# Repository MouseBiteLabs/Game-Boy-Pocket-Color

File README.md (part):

# Game Boy Pocket Color

My <a href="https://github.com/MouseBiteLabs/Game-Boy-DMG-Color">DMGC project</a> put a Game Boy Color put into an original Game Boy shell. But then I said, "Hey! This is neat, but I would rather it be small and cramped and have shorter battery life!" Enter the MGBC, or Pocket Color - a Game Boy Pocket (model name MGB) with the guts of a Game Boy Color (GBC). The PCB here is an original creation with some new features, though the concept and implementation of the "MGBC" or "Pocket Color" has been around for a while! Here are the project goals:

- A Game Boy Pocket aesthetic, using the original Game Boy Pocket shell and interfaces (link port, volume wheel, power switch, etc.), but with the capability of playing both Game Boy and Game Boy Color games.
- A nice, large IPS screen – the GBC Q5 XL IPS Backlight with OSD kit – with brightness and color palette control via the "navigation switch" housed where the contrast wheel used to be. (I will refer to the PCB attached to the Q5 screen as the “Q5 board”)
- A modernized, efficient switch mode power supply that can run off 2x AAA batteries or input from the DC jack, just like the original MGB. Testing shows that playing with NiMH AAA batteries can yield about 3.5 hours of gameplay at normal settings.
- Louder, cleaner sound through a modern audio amplifier.
- The option for tactile switches for the face buttons - like the GBA SP.
- No major externally viewable case modifications, to keep the OEM look and feel, outside of the screen, as much as possible.

All gerbers and source files can be found in this repo, as this project is fully open source. These PCB files and notes about the board, including customizations **and some troubleshooting tips**, can be found in the <a href="https://github.com/MouseBiteLabs/Game-Boy-Pocket-Color/tree/main/MGBC%20PCB#cpu-pin-functions">PCB folder</a>. Technical documentation of the board can be found in the <a href="https://github.com/MouseBiteLabs/Game-Boy-Pocket-Color/tree/main/Technical">Technical folder</a>.

**Do you want to make one?** Then you NEED TO READ this entire page. Seriously. Before asking a question, please review the <a href="https://github.com/MouseBiteLabs/Game-Boy-Pocket-Color#frequently-asked-questions">FAQ</a> at the bottom of the README for answers to.... frequently asked questions. Please try to find your answer in this repository - 95% of the time someone asks me something it's answered here already.

## Disclaimer

Before I go any further, please read this VERY important disclaimer, **IN IT'S ENTIRETY,** if you are thinking about making this yourself. **Don't let this picture happen to you!**

I made this project first and foremost for my own purposes. Nearly all of the features I have included are things I personally wanted. I have tried my hardest to make the project modular, if others would like to improve or change things easily, and I have also tried very hard to make the design somewhat less prone to potential errors during assembly. But in the end, every decision I made was for what I wanted the final product to be, with my skill level in mind.

So if you choose to build this project yourself, be warned - this is a considerably advanced, and expensive build. You must be comfortable with the fact that you may lose or damage expensive components. You are 100% liable for any damage done to your property or yourself. I am not responsible for any damage or loss of property incurred while attempting this project, or after completion of the project - you alone accept all risk. If you're *at all* questioning wether or not you can successfully attempt this project, please first practice with the <a href="https://github.com/MouseBiteLabs/Pocket-Mouse-Power-Board">Pocket Mouse Power Board</a> - this requires no original Game Boy parts, and the total parts cost of the board is less than $10. And before you dismantle a Game Boy, solder the FFC connector on the top of the MGBC board to make sure you are comfortable with long rows of fine pitch pins, as it is the same pin pitch as the much more expensive and important CPU. **If you have any difficulty assembling either the power board or the FFC connector, I highly discourage attempting the rest of the build.**

Furthermore, while I am confident in this design, I cannot claim full compatibility with every system configuration. **Especially if you decide to add a lithium-ion battery.** And there may be latent issues that have yet to crop up. If you see anything I may have missed, or some dubious design choice, feel free to ask questions or comment as such - feedback is appreciated, corrections are welcome.

In summation: **DO NOT attempt this project if you are uncomfortable or inexperienced with detailed electronics troubleshooting, or are not proficient in soldering! This is in NO WAY a beginner's project. You will AT MINIMUM need to be proficient in <a href="https://youtu.be/5uiroWBkdFY?t=110">drag soldering</a> and <a href="https://youtu.be/X3Rc1s6EpSI">hot air reflowing</a>. If you have not gained proficiency in these soldering skills, DO NOT ATTEMPT THIS PROJECT. You accept all risks and costs associated to this build if you choose to attempt it.**

(These parts are *tiny*. Quarter for scale - do not install a quarter in your final build.)

## Bill of Materials (BOM)

There are a handful of categories for the parts you need for this build. Please review all of them! The total BOM cost will come out to anywhere between $100 and $200 (NOT including the cost of a donor Game Boy Color console!) depending on the options you choose, which OEM parts you re-use, and any potential deals you can get on certain parts. Note that with the exception of a few components from a donor Game Boy Color, *most* of the electronic parts are brand new.

### I. Circuit Boards
  
First and foremost, you will need two brand new circuit boards for this build:
- <a href="https://github.com/MouseBiteLabs/Game-Boy-Pocket-Color/tree/main/MGBC%20PCB#mgbc-mbl-01">the main MGBC circuit board</a>, and 
- a power supply board that fits in the U5 socket on the MGBC board (like my <a href="https://github.com/MouseBiteLabs/Pocket-Mouse-Power-Board">Pocket Mouse Power Board</a>, or other power supply boards from other creators - check the <a href="https://github.com/MouseBiteLabs/Game-Boy-Pocket-Color#v-compatibility-with-other-mods">Compatibility</a> section below for more information. )

**I don't recommend using an original power board from a Game Boy!**

Again, I sell <a href="https://mousebitelabs.etsy.com/listing/1459241814/game-boy-pocket-color-pcb-mgbc-mbl-01?utm_source=Copy&utm_medium=ListingManager&utm_campaign=Share&utm_term=so.lmsm&share_time=1694127166906">the MGBC board</a> and <a href="https://mousebitelabs.etsy.com/listing/1473483915/pocket-mouse-power-board?utm_source=Copy&utm_medium=ListingManager&utm_campaign=Share&utm_term=so.lmsm&share_time=1694127201480">my regulator board</a> on my Etsy store. You can alternatively use the files in the MGBC PCB folder to order it yourself. Please see the MGBC PCB folder for more info.

And finally, <a href="https://shop.insidegadgets.com/product/game-boy-pocket-color/">insideGadgets sells these boards partially assembled!</a>

### Information on Older Revisions

The current revision is v2.1, but you may have an earlier board (if you bought one from me, rest assured it will work perfectly fine - most of the changes between for-sale revisions are inconsequential to the end user). The BOM has changed slightly for v1.6 and later boards, compared to previous revisions. Please view the Excel and/or .csv file above for BOM information (or contact me). Here's a short list of information about the older boards, and what is required/recommended when using them:

| Revision | Recommendations |
| ---- | ---------------------------------------------------------------------------------------------------------------------------- |
| v1.0 | You are a masochist. You're on your own for this one.                                                                        |
| v1.1 | Are you me? No? Then did you rob my house?                                                                                   |
| v1.2 | You're one of the beloved beta testers. You didn't build it yet? For shame. Contact me.                                      |
| v1.3 | These should be practice boards only.                                                                                        |
| v1.4 | Use tactile buttons. Minor shell trimming may be required for volume dial and rocker switch.                                 |
| v1.5 | Minor shell trimming may be required for volume dial and rocker switch.                                                      |
| v1.6 | No important differences compared to the latest revision, but check EM7 and DC/BT+ requirements!                             |
| v2.0 | No important differences compared to the latest revision.                                                                    |

### II. Brand New Electronic Parts

The MGBC board uses mostly all-new components. This is not a direct-transfer board. The master BOM with every electronic component required for the main MGBC circuit board is provided in the folder in Excel format. Note that some parts may be out of stock at the links provided, but many can be found at alternate other retailers online, or have a proper substitute. Here is a saved cart from Mouser that contains all the parts in the BOM Excel, including some duplicates: https://www.mouser.com/ProjectManager/ProjectDetail.aspx?AccessID=854e7f6cf9

*Note: This cart link is for v1.6, v2.0, and v2.1 boards. Please check out the BOM Excel or .csv file above for information about v1.5 and earlier.*

Double check to see if any parts are missing, and consider ordering multiples of some parts. Also, there are some parts you may want to remove (like the tactile switches). **If a part is backordered, or out of stock** - check the Excel file, or the BOM listed at the bottom of the MGBC PCB folder. There may be alternate part options listed. You can also check for stock at places like Digikey, Newark, or LCSC. And you can always use Octopart.com to help find in-stock parts at other websites. Please understand that I can't maintain the cart for every out-of-stock part, so please do some research :)

Also note, while I do recommend the board, this BOM does not include parts for the Pocket Mouse Power Board. <a href="https://github.com/MouseBiteLabs/Pocket-Mouse-Power-Board">Please review my github on that board</a> for more information if you wish to use it for your power supply!

### III. Game Boy Electronic Parts

*Despite this being a **Pocket** Color, you don't actually need a Game Boy Pocket. However, this project **does require** at minimum a Game Boy Color.*

There are a handful of parts that I have not located aftermarket substitutes for, and will therefore necessitate an original Game Boy console to salvage from. Please note that removing these parts is not a trivial task, and **requires advanced soldering and desoldering skills to be successful.**

The following parts are required from an original Game Boy Color console:

  -	U1 – CGB CPU (all revisions *except* REV E, which is *incompatible*)
  - X1 – 8.388 MHz crystal oscillator

The following parts are required from an original Game Boy Color **OR** Game Boy Pocket console:

  -	P1 – Cartridge connector
  -	P5 – Headphone jack

The following parts can be salvaged from a Game Boy Color, but newly manufactured commercial off-the-shelf options exist:

  - U2 – LH52256CVTXIZ (SRAM); alternate: https://mou.sr/3f8G0Mi
  - EM10 – input filter; alternate: https://mou.sr/3FiMvXw

The following parts can be salvaged from a Game Boy Color *or* Game Boy Pocket, but aftermarket options exist:

  -	VR1 – Volume dial
  -	SW1 – Power switch
  -	P3 – Link port
  -	P4 – DC jack

### IV. External Build Parts

The following is the high-level BOM - basically, the Game Boy part. Note that parts that deviate from the ones listed here (like different shell designs) might necessitate different fitment modifications, or end up being incompatible. Note that this list is not a comprehensive list of all the places you can get these parts. I encourage you to search around if you can't find what you want here. 

-	**Shell:** I generally recommend the Funnyplaying "IPS Ready" ones if you don't want to trim anything. If you don't use these, then you're on your own for how to prepare it - generally, you can follow guides for preparing a Pocket for an IPS screen kit.
    - RGRS: <a href="https://retrogamerepairshop.com/products/funnyplaying-game-boy-pocket-q5-ips-ready-shell-housing-no-cut?pr_prod_strat=copurchase&pr_rec_id=d8b0186ad&pr_rec_pid=6280907751596&pr_ref_pid=6115075391660&pr_seq=uniform">FunnyPlaying Game Boy Pocket IPS Backlight Ready Shell Housing No Cut</a>
    - FunnyPlaying: <a href="https://funnyplaying.com/collections/product/products/gbp-retro-pixel-ips-coustom-shell?variant=33054643060797">GBP RETRO PIXEL IPS CUSTOM SHELL</a>
-	**Screen Kit:** This is the important one. You need this specific type of kit - the Q5 IPS with OSD. It goes by many names, the maker is Hispeedido (*not* FunnyPlaying). Kits that have the screen laminated to a GBC lens are *not* compatible, but kits that include a lit-up logo on the bottom part of the screen are fine to use. Make sure you DO NOT get the Game Boy Pocket version - it is not compatible! Also, be sure to test this screen kit before installing it, preferrably with an original Game Boy Color. Sometimes they arrive damaged, and once you've installed, it may not be possible to get a refund.
    - RGRS: <a href="https://retrogamerepairshop.com/products/game-boy-color-q5-ips-backlight-with-osd?variant=37646279213228">GBC Q5 XL IPS Backlight with OSD</a> OR <a href="https://retrogamerepairshop.com/collections/gbc-displays/products/game-boy-color-q5-osd-ips-kit-with-color-changing-logo?variant=41819042185388">Game Boy Color Q5 OSD IPS Kit with Color Changing Logo 
    - AliExpress: <a href="https://www.aliexpress.us/item/3256801650459088.html?spm=a2g0o.productlist.main.1.758e53f17WUFK2&algo_pvid=24ef67e3-d608-4269-a663-05eafed1bd17&algo_exp_id=24ef67e3-d608-4269-a663-05eafed1bd17-0&pdp_npi=3%40dis%21USD%2145.9%2145.9%21%21%21%21%21%4021224e9b16816641208271256d074d%2112000017802039303%21sea%21US%210&curPageLogUid=dCymHIE0cr4X">GBC Q5 IPS LCD Kit</a>
    - HHL: <a href="https://handheldlegend.com/products/game-boy-color-ips-lcd-q5-hispeedido">Game Boy Color IPS LCD Q5 - Hispeedido</a>
I have not thoroughly tested it, but the CGS (Cloud Game Store) display should be electrically compatible as of v2.0. It will need some kind of method of centering the image if you choose to use it, though. (At the time of writing, I have heard there is a seller on Taobao selling laminated CGS kits...)
  -	**Lens:** I recommend you get an "IPS Lens" as the viewing area is slightly larger than the OEM one. 
    - RGRS: <a href="https://retrogamerepairshop.com/collections/gbp-lenses-1/products/funnyplaying-game-boy-pocket-ips-retro-pixel-mod-led-hole-glass-screen-lens?variant=37635319988396">FunnyPlaying Game Boy Pocket IPS Retro Pixel Mod LED Hole Glass Screen Lens</a>
    - FunnyPlaying: <a href="https://funnyplaying.com/products/gbp-retro-pixel-ips-glass-lens?_pos=1&_sid=ec7345577&_ss=r&variant=31969857437757">GBP RETRO PIXEL IPS GLASS LENS</a>
- **Buttons:** Funnyplaying models are generally OEM-like (IMO), but you can also use OEM ones. Or any other maker of buttons! (Make sure you get Game Boy *Pocket* buttons - Game Boy *Color* buttons will not fit.)
  - RGRS: <a href="https://retrogamerepairshop.com/collections/gbp-buttons-1/products/funnyplaying-game-boy-custom-pocket-buttons?variant=41432879169708">FunnyPlaying Game Boy Pocket Custom Buttons</a>
  - LabFifteen: <a href="https://labfifteenco.com/collections/game-boy-pocket-buttons">Custom buttons</a>
  - FunnyPlaying: <a href="https://funnyplaying.com/products/gbp-custom-buttons?_pos=2&_sid=1bdf0ccb6&_ss=r&variant=33054652039229">GBP CUSTOM BUTTONS</a>
- **Membranes:** Important, but very forgettable! You will need them even if you install tactile switches.
  - RGRS: <a href="https://retrogamerepairshop.com/collections/gbp-buttons-1/products/funnyplaying-game-boy-pocket-silicone-button-contact-pad-membranes?variant=40593166401708">FunnyPlaying Game Boy Pocket Silicone Button Contact Pad Membranes
  - FunnyPlaying: <a href="https://funnyplaying.com/products/replacement-silicone-pads-for-gbp-mgb?_pos=3&_sid=1bdf0ccb6&_ss=r&variant=39378004705341">GBP/MGB REPLACEMENT SILICONE PADS</a>
- **Speaker:** There are tons of options for this as well, including using the OEM one. Game Boy Color *and* Game Boy Pocket speakers are compatible, since they are the same part.
  - RGRS: <a href="https://retrogamerepairshop.com/collections/gbp-audio/products/funnyplaying-clear-game-boy-color-speaker?variant=37728953761964">FunnyPlaying Clear Game Boy Color & Pocket Speaker</a>
  - FunnyPlaying: <a href="https://funnyplaying.com/products/clear-gbc-mgb-speaker?_pos=1&_sid=2cc6157b6&_ss=r">CLEAR GBC/MGB SPEAKER</a>
- **Battery Tabs:** This one is another part I commonly forget about. You *cannot* use Game Boy Color ones, you *must* use Game Boy Pocket battery terminals. Luckily, they're very easy to find.
  - RGRS: <a href="https://retrogamerepairshop.com/collections/gbp-power/products/gbp-game-boy-pocket-high-quality-replacement-battery-contact-terminals?variant=37893131305132">GBP Game Boy Pocket High Quality Replacement Battery Contact Terminals
- **Stickers:** Completely optional, but they can really bring a build together. Especially if you have custom Pocket Color stickers!
  - Nextstopplease: <a href="https://nextstopplease.square.site/product/gb-pocket-color-label/196?cp=true&sa=true&sbp=false&q=false">GB Pocket Color Label</a>
  - 8bitlabels: <a href="https://www.etsy.com/shop/8bitlabels?ref=simple-shop-header-name&listing_id=1097537372">8bitlabels on Etsy</a>

<b>Buying from RGRS? Consider helping out some cool people with these referral links:</b>
- <a href="https://retrogamerepairshop.com/?ref=ltyD2rUX">CodyWick</a>
- <a href="https://retrogamerepairshop.com/?ref=HSj4v5OO">JackV</a>

<b>Or use one of these other discount codes at checkout:</b>
- Nataliethenerd
- B23N
- Tito

### V. Battery Selection

I developed this system almost exclusively with rechargeable eneloop Pro NiMH AAA batteries. After finishing up development, I tried out regular alkaline AAAs. What I found, and some others have found, is that they are less reliable to use than NiMH batteries, particularly during start-up. When using alkaline batteries, after they have been discharged for an hour or two, sometimes the screen and power LED will flicker for a bit before fully coming on. This also varies between brands - I found Energizer Max batteries to perform much better than Duracell Coppertop batteries, for example. Duracells caused much more stuttering during the start-up sequence. Other brands or types may perform better, but I'm not about to buy a bunch of disposable alkalines to find out which.

However, the rechargeable NiMH AAA batteries I tested *do not* have any of these issues. And I tested these a lot during development, at many different states of charge. They are seemingly better suited for power delivery, and I never experience any kind of stuttering during start-up. I believe this is due to the generally higher internal resistance of alkaline batteries (a quick sampling of popular battery brands show approximately 50 mOhms internal resistance for NiMH chemistry, but 150+ mOhms internal resistance for alkaline chemistry). 

Rechargeable NiMH batteries give you about 3 to 6 hours of gameplay based on your settings and game selection, and as long as you have more than one set, you can easily charge one set while you play with another set. <A href="https://www.amazon.com/Panasonic-BK-4HCCA8BA-eneloop-Pre-Charged-Rechargeable/dp/B00JHKSL0A/ref=sr_1_1_pp?keywords=eneloop%2BAAA&qid=1690853200&sr=8-1&th=1">Here's a listing for the eneloop pro batteries I use in all of my Game Boys.</a> Other brands of rechargeable batteries I have seen used are Ikea LADDA batteries, and Jugee batteries.

#### Lithium Ion Batteries

Lithium-ion batteries (or LiPos) are another option, but I do not fully detail how to use them in this repository. You must be knowledgeable enough on your own to utilize them. Please review the entire repo for crucial information if you *do* decide to go with a LiPo.

I have created <a href="https://github.com/MouseBiteLabs/Pocket-Protector-Power-Board">my own LiPo board</a> to fit in the U5 socket, but I really recommend using AAAs. It will make the assembly easier and safer.

Nataliethenerd's <a href="https://www.nataliethenerd.com/product-page/safer-charge-dc">Safer Charge DC</a> board is also compatible with the MGBC. Instructions for how to use it is in the Testing and Assembly section.
  
### VI. Compatibility with Other Mods

You don't need any extra mods to complete the MGBC build, but there are some options available. One of the goals for the MGBC was to provide compatibility with various mods by other makers. In general, I tried to make the board similar to the Game Boy Pocket PCB in terms of solder points for different kinds of mods. The MGBC will not benefit from any mods that include audio amplification/"cleaning" or tactile button mods, as I've included those improvements already. Check out the <a href="https://github.com/MouseBiteLabs/Game-Boy-Pocket-Color/tree/main/MGBC%20PCB#customization-options">Customization Options</a> section in the MGBC PCB folder for information on those.
  
Here are a sample of my favorite mods for the MGBC:

  - <a href="https://www.etsy.com/listing/1348046388/game-boy-pocket-battery-indicator-mod">Leggomyfroggo's Two-Stage Battery Indicator Mod</a>: goes in place of the power LED, changes color when battery gets low
  - <a href="https://www.etsy.com/listing/1422095615/frogulator-game-boy-colorpocket-dc">Leggomyfroggo's Frogulator</a>: a power supply that slots into the U5 socket; eyes light up for battery power indication
  - <a href="https://www.muramasaentertainment.com/product/pocket-power-pocket/">Muramasa's Pocket-Power Pocket</a>: an all-in-one LiPo charger including USB-C port; requires some shell cuts and **removal of EM7 for v1.6 and earlier** [untested]
  - <a href="https://github.com/marshallh/gbpp">marshallh's Game Boy Pocket Power</a>: a power supply that slots into the U5 socket; has LiPo support (solder wires through the DC and BT+ holes on the MGBC board, and **remove EM7 on v1.6 and earlier** - requires USB-C board for charging and some shell cuts [untested]
  - <a href="https://github.com/skimzor/SZ-REG">skimzor's SZ Regulator</a>: a power supply that slots into the U5 socket; customizable print on the front of the board through <a href="https://ko-fi.com/skimzor">skimzor's Ko-Fi page</a>
  - <a href="https://www.nataliethenerd.com/product-page/gbp-led-boards">Natalie the Nerd's LED Boards</a>: button LED backlight board

Important note for using external mods: you must be aware that the voltage on the SW net (the output of the power switch, connected to pin 1 on the power board socket) will remain connected to the batteries as long as the power switch is on. If your mod connects to the power switch output, then be aware there *will* be a condition where the 5 V on-board is at zero volts, and the battery voltage will still be above 2 V. This may cause issues, such as power draw through resistors even when the power is off, or leakage through protection diodes in certain devices. Please use accordingly.

## Testing and Assembly

I'm going to split this into a few separate sections. This is the general process I follow when assembling an MGBC.

### Circuit Board Assembly

Usually when I'm populating a board, I follow this order:
  
1) Assemble all the non-Gameboy surface mount components first, not including P2, U2, C24, C29, and C45. 
  
2) After soldering these components, I solder the CPU and RAM in, then the FFC connector.
  
3) I use hot air and solder paste to reflow X1, C24, C29, and C45 onto the board. Be sure to either cover the FFC connector with kapton tape to avoid melting the plastic, or heat the board from the bottom.
 
If the build is going to utilize tactile buttons (the ones that are clicky, like on the GBA SP) I install *at least* the start and select ones now. After the headphone jack and DC jack are in, it's tricky to get the start and select tactiles in.
  
4) Finally, I add most of the other external-facing components - VR1, P3, P4, P5, SW1, SW2, D2, the speaker, and the battery terminals. The only parts that I don't populate at this point are the cartridge connector (P1) and the power board (U5). 

**NOTE 1** - Keep VR1 and SW2 as far inside the board as the holes allow. This will reduce interference with the shell. You may need to file away a bit of the shell in order for the knobs to turn freely. It may be a good idea to do a quick fitment test in the shell before going farther into assembly.

**NOTE 2** - You may have to trim the pins on VR1, the volume dial, before soldering. I cut them down in half to make them fit nicer.

### Setting up for AAA vs LiPo

I generally recommend using NiMH AAAs in builds, because they are easier and safer to deal with, they can be swapped in quickly as opposed to waiting for the battery to charge up, and don't require any shell modifications to use (LiPos require a shell cut to fit a USB port, which isn't fun). The only thing you need to do if you're going to use AAAs, which the MGBC is set up for natively, is connect the two holes labelled BT+ and DC together with a wire or 0 ohm resistor. This is also only required on v2.0 and later boards - v1.6 and earlier do not require this. Shorting these holes together connects the DC jack to the input of the regulator. So if you forget to add it, then your DC jack won't work (which may or may not matter to you anyway). **DO NOT SHORT THESE TOGETHER IF USING A LITHIUM-ION BATTERY.**

If you really want to add LiPo support to your build, you're on your own for figuring out how to set it up. The important thing to note on the MGBC board is, for boards v1.6 and earlier, **DO NOT INCLDE EM7**. This component must be removed from the final build. Make absolutely sure you do this - failure to do so may damage your battery and/or system. In version 2.0, you must include EM7 on every build.

Also, to get the power LED to dim at the correct time, remove R6 from the main MGBC board.

If you're using Nataliethenerd's <a href="https://www.nataliethenerd.com/product-page/safer-charge-dc">Safer Charge DC</a>, connect a wire from the "To F1" pad on the back of the board to the BT+ hole on the MGBC, and a wire from the "To 5V" pad on the back of the board to the pad on the USB-C breakout board. Then install the board into the U5 socket as normal.

And, as a mandatory disclaimer, **LITHIUM-ION BATTERIES ARE DANGEROUS. USE AT YOUR OWN RISK. I AM NOT RESPONSIBLE FOR YOUR HOUSE BURNING DOWN. YOU ARE RESPONSIBLE FOR FIGURING OUT HOW TO USE A LIPO ON THIS BOARD.**

### Testing the Power Board and IPS Kit
  
The next step to test is the power board, or U5. If you are using my LiPo power board, the steps to test that board are detailed <a href="https://github.com/MouseBiteLabs/Pocket-Protector-Power-Board">in the repository.</a> I *highly* suggest making sure you've assembled the power board correctly before directly connecting it and powering it all on, cowboy style. If you're able to test your power board before installation, definitely do that, but if you're not sure how, or don't have the ability, then you can actually use your mostly-assembled MGBC board to test it. 
  
Solder wires on pins 1, 2, and 3 from the MGBC board to the power board (the left three holes of the power board). Don't connect the other side of four pins just yet - pin 7 is the 5 V pin, which powers the rest of the Game Boy. Keeping pin 7 depopulated, you can place the Game Boy in the back half of the shell to connect up batteries, or use a power supply clipped to the battery terminals. Turn the power switch on. Use a multimeter to measure the voltage from pin 7 (positive test probe) to GND (negative test probe). You should read approximately 5 V here - anything more than 5.1 V or less than 4.9 V means you've likely got something wrong on your power board.
  
(In this picture, the red circle is pin 7, the blue circle is pin 3, or GND - this is for illustrative purposes only, I recommend testing the board before fully mounting it to the MGBC board.)

If you confirm you have 5 V on pin 7, then remove the wires and connect the board via header pins (if not, check the next section for some troubleshooting advice). Finally, you'll want to test the screen kit. Slide the FFC cable into P2 on the MGBC board, and make sure the cable is all the way in and the bale is pushed all the way down. Let the screen hang over the front of the board. I recommend placing something insulative - like a piece of paper, or kapton tape - over the empty holes of the cart connector, to prevent the back of the display from shorting on the pins. If you have a power supply, you can use that to power it on the battery terminals (set it for 3 V, 1.5 A). If not, you can again put the Game Boy in the back half of a Game Boy Pocket shell to use batteries. (I have mixed results with using battery holders with alligator clips.)

Turn it on, and check for these things:
  
1) Power LED turns on
2) The speaker makes the start-up ding (use headphones to check both left and right channels, and check the volume)
3) The screen shows the GBC splash logo
  
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
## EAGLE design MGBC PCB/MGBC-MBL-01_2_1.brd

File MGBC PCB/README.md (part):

# MGBC-MBL-01

Version 2.1:

Version 2.0S:

*Note: The v2.0 and v2.1 boards are nearly identical - the only difference is v2.1 has a notch cut in the bottom by the regulator.*

This is the main circuit board in the MGBC build. This README will provide instructions for how to customize the build to your liking, as well as attempt to clear up any questions you may have about the build process.

## Board Characteristics and Order Information

The zipped folder contains all the gerber files for this board, if you wish to order it from a board manufacturer yourself. Version 2.x refers to the PCB that is one solid color with little-to-no visible silkscreen on the front after assembly; Version 2.xS refers to the PCB that has the bottom half filled with slikscreen, to make it look like OEM Pocket boards.

-	Layers: 2
-	Thickness: 1 mm
-	Surface Finish: ENIG (or HASL, which is only acceptable if you are installing tactile buttons)
-   **NOTE: When ordering PCBs, add this note to the order: "The file milling.gbr contains outlines for plated slots. Please add plated slots on the PCB according to this layer."**

You can use the zipped folder at any board fabricator you like. You may also buy the board from PCBWay using these links (disclosure: I receive 10% of the sale value to go towards future PCB orders).

**Solid color version:**

**Half-silkscreen version:**

### Purchase from My Website

You can purchase this circuit board at my website, [https://mousebitelabs.store](https://mousebitelabs.store). Click the following image to be directed to the specific item listing:

### Purchase from Etsy

I also offer the board on Etsy, if you would rather purchase through there - click the banner to be redirected.

## Customization Options

This section will explain all of the different customization options available on this board while you assemble.

### Enabling Reset Button Functionality

Bridge the pads labelled "RST" with solder to turn the navigation switch into a reset button whenever you push it in. It's not particularly easy to push the button in, so accidental resets shouldn't be a concern. But if you find yourself accidentally resetting the system, you can remove the solder from the pads to disable it.

### Power LED Brightness

Increase the value of R9 to decrease the brightness of the power LED during normal battery levels. Increase the value of R10 to decrease the brightness of the power LED during low battery levels. It is suggested to try changing resistances in ~10 kΩ increments.

### Tactile Switches

If you want clicky buttons, like the GBA SP has, then you can install tactile switches onto the button contacts. These are listed as B1-B8 on the BOM. There are three levels of clickiness to choose from, depending on the part number you select - SKRRAAE010 is the "least clicky" with 1 N operating force, SKRRABE010 has 1.6 N of operating force, and SKRRACE010 is the "most clicky" with 2 N of operating force. Note when installing the switches to make sure the little "wings" are oriented correctly as indicated on the board!

### Enabling the DC Jack (v2.0 and v2.1 only)

When making the system for use with AAAs, you must connect the two holes labelled BT+ and DC together with a wire or 0 ohm resistor. This is only required on v2.0 and later boards - v1.6 and earlier do not require this. Shorting these holes together connects the DC jack to the input of the regulator. So if you forget to add it, then your DC jack won't work (which may or may not matter to you anyway). DO NOT SHORT THESE TOGETHER IF USING A LITHIUM-ION BATTERY.

### LiPo Support

Are you using the Game Boy Pocket Power regulator for U5 for LiPo support? Are you sure you want to? Lithium-ion batteries are **dangerous** so if you're going to be using one... you're on your own. You're responsible for using it safely. 

But, I did make it *slightly* easier for you. If you're using either <a href="https://github.com/MouseBiteLabs/Pocket-Protector-Power-Board/blob/main/README.md">my LiPo board</a> or the GBPP with LiPo, solder wires or headers from the DC and BT+ holes into the power board, thread the wires from the battery through the hole in the board to the power board connections, and remember to **REMOVE EM7** if your board revision is v1.6 or earlier. On v2.0 and v2.1, keep EM7 in place. You'll also need a USB-C adapter PCB to go in place of DC jack.

Also, to get the power LED to dim at the correct time, remove R6 from the main MGBC board.

If you're using Nataliethenerd's <a href="https://www.nataliethenerd.com/product-page/safer-charge-dc">Safer Charge DC</a>, connect a wire from the "To F1" pad on the back of the board to the BT+ hole on the MGBC, and a wire from the "To 5V" pad on the back of the board to the pad on the USB-C breakout board. Then install the board into the U5 socket as normal.

## Assembly References

Here are a few images that should help clarify the build process, as well as provide some brief technical explanations to guide you in troubleshooting any errors you might have.

### Part Placement

Some of the parts are a bit cramped, and it can be a bit difficult to decipher which part is which. Hopefully this image helps you clarify. (This is a photo from a previous version of the board, so the parts on your board may be slightly nudged from where they are in this image.)

### CPU Pin Functions

This is a bit of a mess, but depending on the problem you're encountering, it could be worth reflowing the pins on the CPU that correspond to the aspect you're having problems with.
- For miscolored screens, reflow the top display pins.
- For *glitchy* screens, or frozen/all-white screens, reflow the SRAM pins.
- If you're missing button inputs, reflow the bottom left corner button pins.
- If you have games that don't start up properly and hang at the Nintendo logo during start-up, display a glitchy Nintendo logo, or randomly freeze during gameplay, reflow the cartridge pins and clean your cartridge connector. The freezing may also be caused by poorly connected SRAM as well.
- Three link port pins are on the bottom right, but there is one lone one at the top.
- In general, reflowing the clock and power pins (colored red, pink, and black) can solve problems as well.

## PCB Errors

### v1.6 and earlier
- The up/down text for the rocker switch functions is flipped
### v1.5 and earlier
- The rocker switch can sometimes interfere with the shell. Light trimming on the shell may be required for smooth rocking.
- The BOM for builds v1.5 and earlier is different than the one currently in this repo. Please view the differences in the Excel or .csv file in the root directory.
### v1.4
- The button contacts are too responsive compared to Nintendo's button style. Use of tactile switches is recommended.

## Bill of Materials

This should be for reference only. This can be found in the main folder in Excel format. There is also a link in the main folder for a saved Mouser cart with all these parts.

*Note that this reflects the BOM for v1.6 and later. For earlier revisions, see the BOM Excel or .csv in the root folder of the repository.*

| Reference Designators            | Qty | Value/Part Number | Package     | Description        | Comment                                                                                                           | Source                                                                                                                                                                                                                                                                                                                       |
| -------------------------------- | --- | ----------------- | ----------- | ------------------ | ----------------------------------------------------------------------------------------------------------------- | ---------------------------------------------------------------------------------------------------------------------------------------------------------------------------------------------------------------------------------------------------------------------------------------------------------------------------- |
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
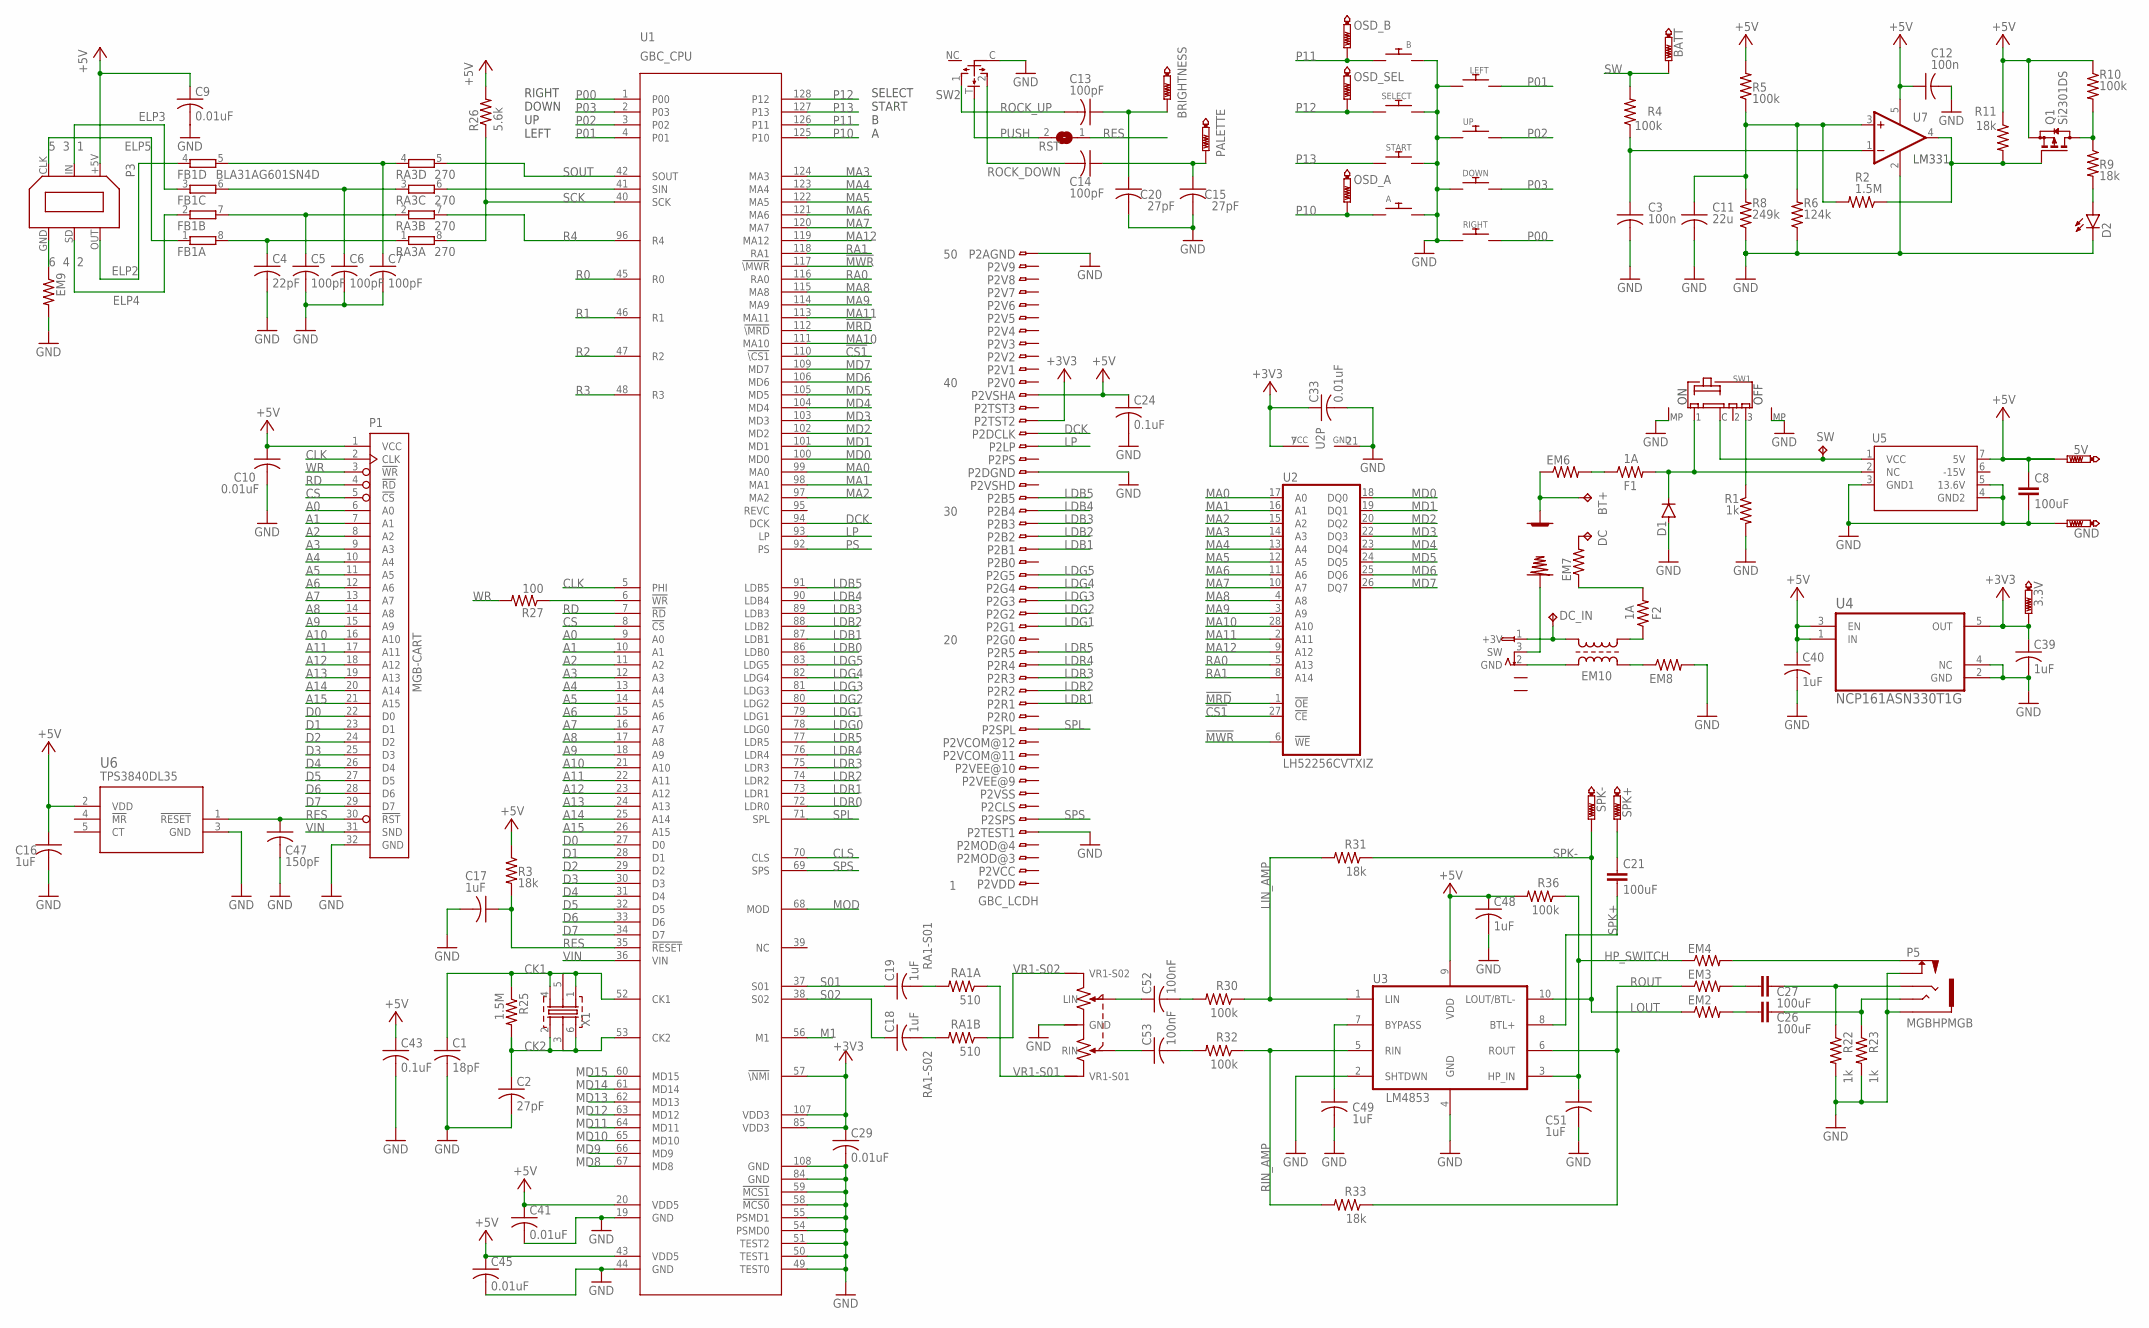
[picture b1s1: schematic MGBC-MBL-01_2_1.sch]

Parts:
3.3V, 5V: PTR1B1,27; B1,27
+: MGB+BATTERY4
-: MGB-BATTERY4
A: DMG-BTN; DMG_BTN3
B: DMG-BTN; DMG_BTN3
BATT: PTR1TP20R; TP20R
BRIGHTNESS: PTR1TP20R; TP20R
BT+: TPPAD1-13; P1-13
C1: 18pF; C0603
C2, C15, C20: 27pF; C0603
C3, C12: 100n; C0603
C4: 22pF; C0603
C5, C6, C7, C13, C14: 100pF; C0603
C8, C21, C26, C27: 100uF; C1210
C9, C10, C29, C33, C41, C45: 0.01uF; C0603
C11: 22u; C0805
C16, C17, C18, C19, C39, C40, C48, C49, C51: 1uF; C0603
C24, C43: 0.1uF; C0603
C47: 150pF; C0603
C52, C53: 100nF; C0603
D1: CGRM4001-G; SOD-123_MINI-SMA
D2: LED3MM
DC: TPPAD1-13; P1-13
DC_IN: TPTP20R; TP20R
DOWN: DMG-BTN; MGB_BTN1_2
EM2, EM3, EM4, EM9: BLM18BD102SN1D; R0603
EM6, EM7, EM8: Z0805C221BPWZT; R0805
EM10: ACM4532-801-2PA; ACM4532
F1, F2: 1A; R0603
FB1: BLA31AG601SN4D; EXB38V
GND: PTR1B1,27; B1,27
LEFT: DMG-BTN; MGB_BTN1_2
OSD_A: PTR1TP20R; TP20R
OSD_B: PTR1TP20R; TP20R
OSD_SEL: PTR1TP20R; TP20R
P1: MGB-CART
P2: GBC_LCDH; 62684-502100AHLF
P3: LINKPORTDMG-LINK-SHORT; CGB-LINK
P4: MGB-PWRJACK
P5: MGBHPMGB; MGB-HEADPHONE
PALETTE: PTR1TP20R; TP20R
Q1: BSS84; SOT23
R1, R22, R23: 1k; R0603
R2, R25: 1.5M; R0603
R3, R9, R11, R31, R33: 18k; R0603
R4, R5, R10, R30, R32, R36: 100k; R0603
R6: 124k; R0603
R8: 249k; R0603
R26: 5.6k; R0603
R27: 100; R0603
RA1A, RA1B: 510; R0603
RA3: 270; EXB38V
RIGHT: DMG-BTN; MGB_BTN1_2
RST: SJ
SELECT: DMG-BTN; DMG_BTN1_W2
SPK+: PTR1PAD1-13; P1-13
SPK-: PTR1PAD1-13; P1-13
START: DMG-BTN; DMG_BTN1_W2
SW: TPTP20R; TP20R
SW1: MGB-SW1; MGB-SWITCH
SW2: NAV_SWITCH
U1: GBC_CPU; QFP-128
U2: LH52256CVTXIZ; TSOP1-28
U3: LM4853; VSSOP10
U4: TLV70233QDBVRQ1; SOT95P280X145-5N
U5: MGB-PWR_BD; MGB-PWRBD
U6: TPS3840; SOT-23-5
U7: TL331; DBV-R-PDSO-G5
UP: DMG-BTN; MGB_BTN1_2
VR1: MGB-POT""; MGB-POT
X1: 8.388608MHZ12SMX-B-4-PAD; 7.5X5-4-PAD

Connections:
!CS1: U1.110 (!\CS1), U2.27 (!CE)
!MRD: U1.112 (!\MRD), U2.1 (!OE)
!MWR: U1.117 (!\MWR), U2.6 (!WE)
+3V3: 3.3V.TP, C29.1, C33.1, C39.1, P2.37, U1.57 (!\NMI), U1.85 (VDD3), U1.107 (VDD3), U2.7 (VCC), U4.5 (OUT)
+5V: 5V.TP, C8.1, C9.1, C10.1, C12.1, C16.1, C24.1, C40.1, C41.1, C43.1, C45.1, C48.1, P1.1 (VCC), P2.39, P3.+5V, Q1.2 (S), R3.1, R5.2, R10.1, R11.1, R26.2, R36.2, U1.20 (VDD5), U1.43 (VDD5), U3.9 (VDD), U4.1 (IN), U4.3 (EN), U5.7 (5V), U6.2 (VDD), U7.5 (V+)
-15V: U5.6 (-15V)
A0: P1.6 (A0), U1.9 (A0)
A1: P1.7 (A1), U1.10 (A1)
A2: P1.8 (A2), U1.11 (A2)
A3: P1.9 (A3), U1.12 (A3)
A4: P1.10 (A4), U1.13 (A4)
A5: P1.11 (A5), U1.14 (A5)
A6: P1.12 (A6), U1.15 (A6)
A7: P1.13 (A7), U1.16 (A7)
A8: P1.14 (A8), U1.17 (A8)
A9: P1.15 (A9), U1.18 (A9)
A10: P1.16 (A10), U1.21 (A10)
A11: P1.17 (A11), U1.22 (A11)
A12: P1.18 (A12), U1.23 (A12)
A13: P1.19 (A13), U1.24 (A13)
A14: P1.20 (A14), U1.25 (A14)
A15: P1.21 (A15), U1.26 (A15)
BATT: +.P$1, +.P$2, +.P$3, BT+.TP, EM6.1
BATT_LVL: Q1.1 (G), R2.1, R11.2, U7.4 (OUT)
BATT_SENSE: C3.1, R4.1, U7.1 (-IN)
BATT_TH: C11.1, R2.2, R5.1, R6.2, R8.2, U7.3 (+IN)
CK1: C1.1, R25.1, U1.52 (CK1), X1.1, X1.4, X1.5
CK2: C2.1, R25.2, U1.53 (CK2), X1.2, X1.3, X1.6
CLK: P1.2 (CLK), U1.5 (PHI)
CLS: U1.70 (CLS)
CS: P1.5 (!CS), U1.8 (!CS)
D0: P1.22 (D0), U1.27 (D0)
D1: P1.23 (D1), U1.28 (D1)
D2: P1.24 (D2), U1.29 (D2)
D3: P1.25 (D3), U1.30 (D3)
D4: P1.26 (D4), U1.31 (D4)
D5: P1.27 (D5), U1.32 (D5)
D6: P1.28 (D6), U1.33 (D6)
D7: P1.29 (D7), U1.34 (D7)
DCK: P2.36, U1.94 (DCK)
ELP2: FB1.4 (1), P3.OUT
ELP3: FB1.3 (1), P3.IN
ELP4: FB1.2 (1), P3.SD
ELP5: FB1.1, P3.CLK
EM10_GND: EM10.3, P4.2 (GND)
EM10_POS: DC_IN.TP, EM10.4, P4.1 (+3V)
GND: A.P$2, B.P$1, C1.2, C2.2, C3.2, C4.2, C5.2, C6.2, C7.2, C8.2, C9.2, C10.2, C11.2, C12.2, C15.2, C16.2, C17.2, C20.2, C24.2, C29.2, C33.2, C39.2, C40.2, C41.2, C43.2, C45.2, C47.2, C48.2, C49.2, C51.2, D1.A, D2.K (C), DOWN.P$2, EM8.2, EM9.2, GND.TP, LEFT.P$2, P1.32 (GND), P2.5, P2.33, P2.50, P3.P$7 (GND), P3.P$10 (GND), P5.GND (S), P5.SWGND (SWB), R1.2, R6.1, R8.1, R22.2, R23.2, RIGHT.P$1, SELECT.P$1, START.P$1, SW1.P$MP1 (MP1), SW1.P$MP2 (MP2), SW2.C, U1.19 (GND), U1.44 (GND), U1.49 (TEST0), U1.50 (TEST1), U1.51 (TEST2), U1.54 (PSMD0), U1.55 (PSMD1), U1.58 (!MCS0), U1.59 (!MCS1), U1.84 (GND), U1.108 (GND), U2.21 (GND), U3.2 (SHTDWN), U3.4 (GND), U4.2 (GND), U4.4 (NC), U5.3 (GND1), U5.4 (GND2), U5.5 (13.6V), U6.3 (GND), U7.2 (GND), UP.P$1, VR1.P$1 (GND), VR1.P$6 (GND), VR1.P$7 (GND)
HP_SWITCH: C51.1, EM4.1, R36.1, U3.3 (HP_IN)
LDB0: U1.86 (LDB0)
LDB1: P2.27, U1.87 (LDB1)
LDB2: P2.28, U1.88 (LDB2)
LDB3: P2.29, U1.89 (LDB3)
LDB4: P2.30, U1.90 (LDB4)
LDB5: P2.31, U1.91 (LDB5)
LDG0: U1.78 (LDG0)
LDG1: P2.21, U1.79 (LDG1)
LDG2: P2.22, U1.80 (LDG2)
LDG3: P2.23, U1.81 (LDG3)
LDG4: P2.24, U1.82 (LDG4)
LDG5: P2.25, U1.83 (LDG5)
LDR0: U1.72 (LDR0)
LDR1: P2.15, U1.73 (LDR1)
LDR2: P2.16, U1.74 (LDR2)
LDR3: P2.17, U1.75 (LDR3)
LDR4: P2.18, U1.76 (LDR4)
LDR5: P2.19, U1.77 (LDR5)
LIN_AMP: R30.1, R31.2, U3.1 (LIN)
LP: P2.35, U1.93 (LP)
M1: U1.56 (M1)
MA0: U1.99 (MA0), U2.17 (A0)
MA1: U1.98 (MA1), U2.16 (A1)
MA2: U1.97 (MA2), U2.15 (A2)
MA3: U1.124 (MA3), U2.14 (A3)
MA4: U1.123 (MA4), U2.13 (A4)
MA5: U1.122 (MA5), U2.12 (A5)
MA6: U1.121 (MA6), U2.11 (A6)
MA7: U1.120 (MA7), U2.10 (A7)
MA8: U1.115 (MA8), U2.4 (A8)
MA9: U1.114 (MA9), U2.3 (A9)
MA10: U1.111 (MA10), U2.28 (A10)
MA11: U1.113 (MA11), U2.2 (A11)
MA12: U1.119 (MA12), U2.9 (A12)
MD0: U1.100 (MD0), U2.18 (DQ0)
MD1: U1.101 (MD1), U2.19 (DQ1)
MD2: U1.102 (MD2), U2.20 (DQ2)
MD3: U1.103 (MD3), U2.22 (DQ3)
MD4: U1.104 (MD4), U2.23 (DQ4)
MD5: U1.105 (MD5), U2.24 (DQ5)
MD6: U1.106 (MD6), U2.25 (DQ6)
MD7: U1.109 (MD7), U2.26 (DQ7)
MD8: U1.67 (MD8)
MD9: U1.66 (MD9)
MD10: U1.65 (MD10)
MD11: U1.64 (MD11)
MD12: U1.63 (MD12)
MD13: U1.62 (MD13)
MD14: U1.61 (MD14)
MD15: U1.60 (MD15)
MOD: U1.68 (MOD)
unnamed: C7.1, FB1.5 (2), RA3.4 (1)
unnamed: C6.1, FB1.6 (2), RA3.3 (1)
unnamed: D2.A, R9.2
unnamed: C52.2, R30.2
unnamed: C53.2, R32.2
unnamed: C5.1, FB1.7 (2), RA3.2 (1)
unnamed: C52.1, VR1.P$3 (LIN)
unnamed: R27.1, U1.6 (!WR)
unnamed: C4.1, FB1.8 (2), RA3.1
unnamed: C53.1, VR1.P$2 (RIN)
unnamed: R1.1, SW1.P$3 (3)
unnamed: DC.TP, EM7.2
unnamed: EM7.1, F2.2
unnamed: D1.C, F1.2, SW1.P$1 (1), U5.2 (NC)
unnamed: EM6.2, F1.1
unnamed: EM10.1, F2.1
unnamed: RA3.6 (2), U1.41 (SIN)
unnamed: Q1.3 (D), R9.1, R10.2
unnamed: EM8.1, EM10.2
unnamed: BRIGHTNESS.TP, C13.1, C20.1
unnamed: EM9.1, P3.GND
unnamed: C14.1, C15.1, PALETTE.TP
unnamed: C49.1, U3.7 (BYPASS)
unnamed: EM4.2, P5.SW (SWA)
unnamed: C27.2, P5.R, R22.1
unnamed: C26.2, P5.L (T), R23.1
unnamed: C26.1, EM2.2
unnamed: C27.1, EM3.2
unnamed: C21.1, SPK+.TP
P00: RIGHT.P$2, U1.1 (P00)
P01: LEFT.P$1, U1.4 (P01)
P02: U1.3 (P02), UP.P$2
P03: DOWN.P$1, U1.2 (P03)
P10: A.P$1, OSD_A.TP, U1.125 (P10)
P11: B.P$2, OSD_B.TP, U1.126 (P11)
P12: OSD_SEL.TP, SELECT.P$2, U1.128 (P12)
P13: START.P$2, U1.127 (P13)
PS: U1.92 (PS)
PUSH: RST.2, SW2.T
R0: U1.45 (R0)
R1: U1.46 (R1)
R2: U1.47 (R2)
R3: U1.48 (R3)
R4: RA3.7 (2), U1.96 (R4)
RA0: U1.116 (RA0), U2.5 (A13)
RA1: U1.118 (RA1), U2.8 (A14)
RA1-S01: C19.2, RA1A.2
RA1-S02: C18.2, RA1B.2
RD: P1.4 (!RD), U1.7 (!RD)
RES: C17.1, C47.1, P1.30 (!RST), R3.2, RST.1, U1.35 (!RESET), U6.1 (!RESET)
RIN_AMP: R32.1, R33.2, U3.5 (RIN)
ROCK_DOWN: C14.2, SW2.2
ROCK_UP: C13.2, SW2.1
ROUT: EM3.1, R33.1, U3.6 (ROUT)
S01: C19.1, U1.37 (S01)
S02: C18.1, U1.38 (S02)
SCK: R26.1, RA3.8 (2), U1.40 (SCK)
SOUT: RA3.5 (2), U1.42 (SOUT)
SPK+: C21.2, U3.8 (BTL+)
SPK-: EM2.1, R31.1, SPK-.TP, U3.10 (LOUT/BTL-)
SPL: P2.13, U1.71 (SPL)
SPS: P2.6, U1.69 (SPS)
SW: BATT.TP, R4.2, SW.TP, SW1.P$C (C), U5.1 (VCC)
SW1B: -.P$1, -.P$3, -.P$4, P4.3 (SW)
VIN: P1.31 (SND), U1.36 (VIN)
VR1-S01: RA1A.1, VR1.P$5 (VR1-S01)
VR1-S02: RA1B.1, VR1.P$4 (VR1-S02)
WR: P1.3 (!WR), R27.2

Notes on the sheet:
5 3 1
6 4 2
SELECT START B A
RIGHT DOWN UP LEFT
TPS3840DL35
LOUT
LM331
Si2301DS
NCP161ASN330T1G

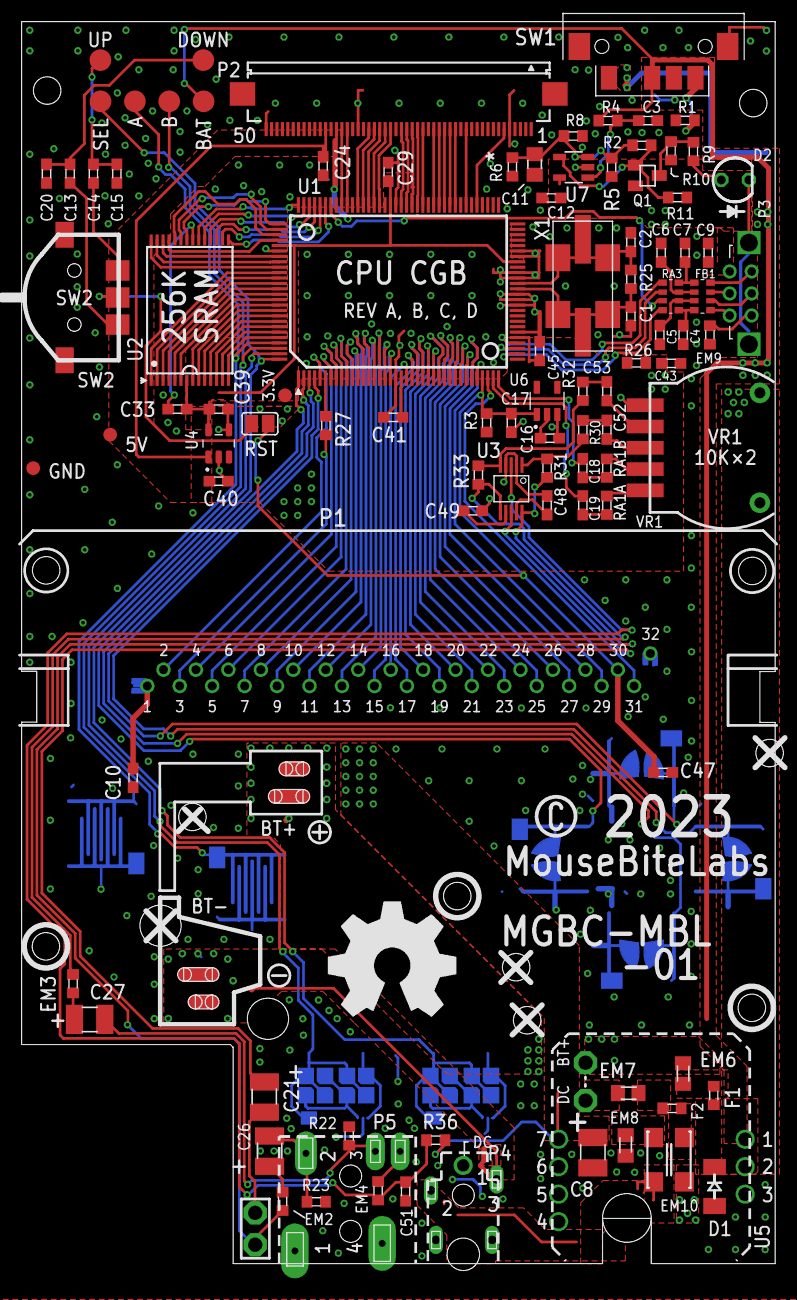
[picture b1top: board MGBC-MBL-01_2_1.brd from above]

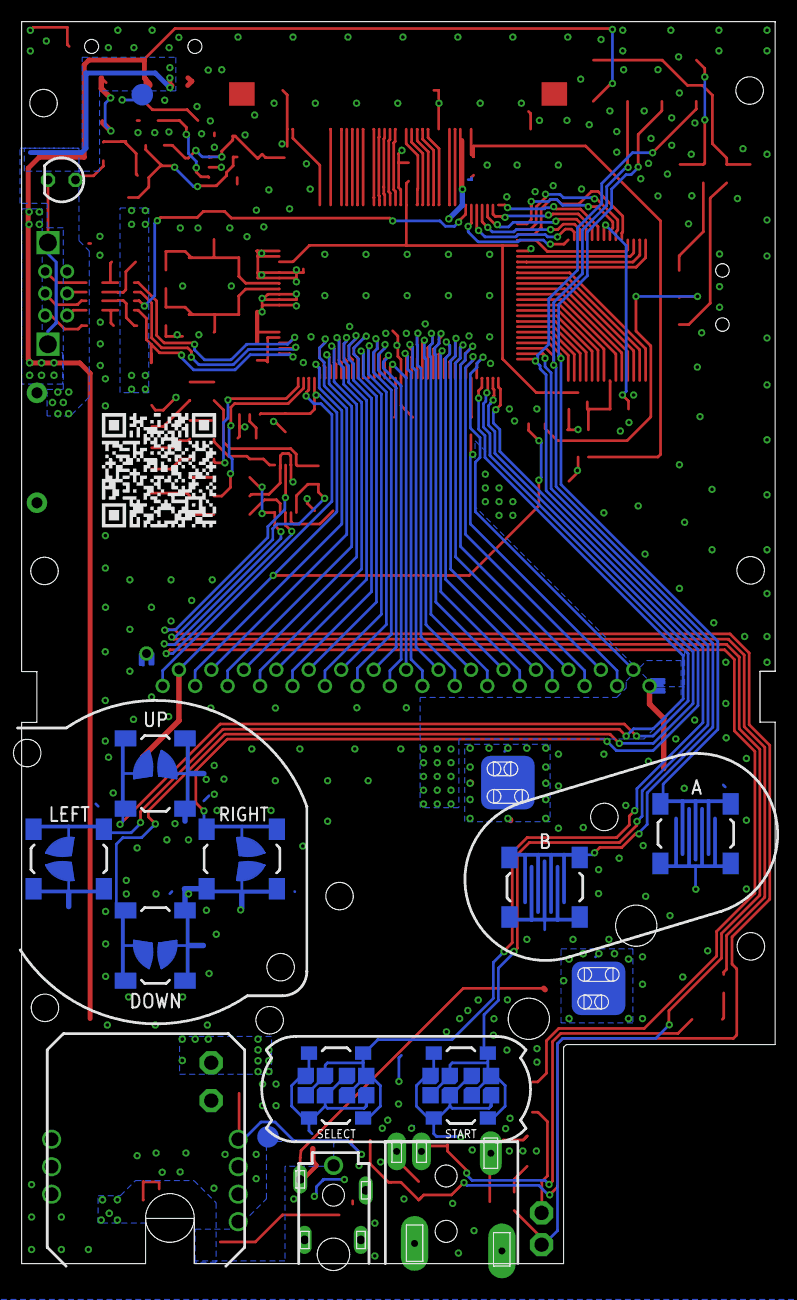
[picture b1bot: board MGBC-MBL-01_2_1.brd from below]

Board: 2 copper layers, 69.6 x 114.8 mm, 116 parts (11 on the bottom side), 147 nets.

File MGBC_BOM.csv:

,,,,,Cart link:,https://www.mouser.com/ProjectManager/ProjectDetail.aspx?Acc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,
Reference Designators,Qty,Value/Part Number,Package,Description,Comment,Source,
B1-B8,8,SKRRABE010,,Tactile switch,"Optional, can be omitted if you don't want clicky SP-style buttons (SKRRAA is less clicky, SKRRAC is more clicky)",https://www.mouser.com/ProductDetail/688-SKRRAB,
"BT+, BT-",2,,,Battery terminals,Can be salvaged from MGB instead,https://retrogamerepairshop.com/collections/gbp-power/produc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,
C1,1,18pF,0603,Capacitor (MLCC),Should be X5R (or better); at least 1% tolerance; at least 16V,https://www.mouser.com/ProductDetail/YAGEO/CC0603FRNPO9BN180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,
"C2, C15, C20",3,27pF,0603,Capacitor (MLCC),Should be X5R (or better); at least 1% tolerance; at least 16V,https://www.mouser.com/ProductDetail/603-C0603FRNPO9BN270,
"C3, C12, C24, C43, C52, C53",6,0.1uF,0603,Capacitor (MLCC),"Should be X5R (or better), at least 16V",https://www.mouser.com/ProductDetail/KEMET/C0603C104M3RACTU?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,
C4,1,22pF,0603,Capacitor (MLCC),,https://www.mouser.com/ProductDetail/YAGEO/CC0603JRNPO9BN220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,
"C5-C7, C13, C14",5,100pF,0603,Capacitor (MLCC),,https://www.mouser.com/ProductDetail/YAGEO/CC0603JPNPO9BN101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,
"C8, C21, C26, C27",4,100uF,1210,Capacitor (Tant),,https://www.mouser.com/ProductDetail/?qs=rmxM1XIQazfTOF9DkZj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,
"C9, C10, C29, C33, C41, C45",6,0.01uF,0603,Capacitor (MLCC),"Should be X5R (or better), at least 16V",https://www.mouser.com/ProductDetail/KEMET/C0603C103J5RACTU?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,
C11,1,22uF,0805,Capacitor (MLCC),,https://www.mouser.com/ProductDetail/Murata-Electronics/GRM2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,
"C16-C19, C39, C40, C48, C49, C51",9,1uF,0603,Capacitor (MLCC),"Should be X5R (or better), at least 16V",https://www.mouser.com/ProductDetail/KEMET/C0603C105K3PACTU?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,
C47,1,150pF,0603,Capacitor (MLCC),,https://www.mouser.com/ProductDetail/KEMET/C0603C151J5GACTU?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,
D1,1,PMEG2010AEH,SOD-123,Schottky diode,"Most schottky diodes should be suitable (at least 1A, 16V)",https://www.mouser.com/ProductDetail/?qs=LOCUfHb8d9u7lcjEnyh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,
D2,1,151033RS03000,3mm,Red LED,,https://www.mouser.com/ProductDetail/Wurth-Elektronik/151033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,
"EM2-EM4, EM9",4,BLM18BD102SN1D,0603,Filter,,https://www.mouser.com/ProductDetail/Murata-Electronics/BLM1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,
EM6-EM8,3,LCMGA201208T221RG,0805,Filter,Replacement: Z0805C221BPWZT,https://www.mouser.com/ProductDetail/TAIYO-YUDEN/LCMGA201208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,
EM10,1,744235601,1812,Common mode filter,Can be salvaged from CGB instead,https://www.mouser.com/ProductDetail/Wurth-Elektronik/744235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,
"F1, F2",2,1A,0603,Fuse,,https://www.mouser.com/ProductDetail/Vishay-Beyschlag/MFU060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,
FB1,1,BLA31AG601SN4D,1206,Ferrite Bead,,https://www.mouser.com/ProductDetail/Murata-Electronics/BLA3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,
P1,1,,,Cart connector,,Salvaged (MGB/CGB),
P2,1,62684-502100AHLF,,FFC connector,Can be salvaged from CGB instead,https://www.mouser.com/ProductDetail/?qs=HL%252BYNjdyZ0vzwc9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,
P3,1,,,Link port,Can be salvaged from MGB/CGB instead,https://retrogamerepairshop.com/collections/gbp-accessories/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,
P4,1,,,DC Jack,Can be salvaged from MGB/CGB instead,https://www.aliexpress.us/item/2255800460672253.html?spm=a2g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,
P5,1,,,Headphone jack,,Salvaged (MGB/CGB),
Q1,1,SI2301CDS,SOT23,P-channel MOSFET,,https://www.mouser.com/ProductDetail/781-SI2301CDS-E3,
"R1, R22, R23",3,1k,0603,Resistor,,https://www.mouser.com/ProductDetail/YAGEO/RC0603FR-071KL?qs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,
"R2, R25",2,1.5M,0603,Resistor,Recommended at least 1% tolerance,https://www.mouser.com/ProductDetail/YAGEO/RC0603FR-071M5L?q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,
"R3, R9, R11, R31, R33",5,18k,0603,Resistor,,https://www.mouser.com/ProductDetail/YAGEO/RC0603FR-1018KL?q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,
"R4, R5, R10, R30, R32, R36",6,100k,0603,Resistor,,https://www.mouser.com/ProductDetail/YAGEO/RC0603FR-07100KL?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,
R6,1,124k,0603,Resistor,,https://www.mouser.com/ProductDetail/YAGEO/RC0603FR-07124KL?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,
R8,1,249k,0603,Resistor,,https://www.mouser.com/ProductDetail/YAGEO/RC0603FR-07249KL?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,
R26,1,5.6k,0603,Resistor,,https://www.mouser.com/ProductDetail/YAGEO/RC0603FR-075K6L?q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,
R27,1,100,0603,Resistor,,https://www.mouser.com/ProductDetail/YAGEO/RC0603FR-07100RL?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,
"RA1A, RA1B",2,510,0603,Resistor,,https://www.mouser.com/ProductDetail/YAGEO/RC0603FR-07510RL?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,
RA3,1,270 (x4),1206,Resistor,,https://www.mouser.com/ProductDetail/YAGEO/TC164-JR-07270RL?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,
SP,1,,,Speaker,Can be salvaged from MGB/CGB instead,https://retrogamerepairshop.com/collections/gbp-audio/produc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,
SW1,1,,,Power switch,,Salvaged (MGB/CGB),
SW2,1,COM-08184,,Navigation switch,,https://www.mouser.com/ProductDetail/SparkFun/COM-08184?qs=W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,
U1,1,GBC CPU,QFP-128,CPU,,Salvaged (GBC),
U2,1,LH52256CVTXIZ,TSOP-28,RAM,Can be salvaged from CGB instead,https://mou.sr/3f8G0Mi,
U3,1,LM4853,VSSOP-10,Audio amplifier,,https://www.mouser.com/ProductDetail/Texas-Instruments/LM485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,
U4,1,NCP161ASN330T1G,SOT23-5,LDO,"Can also use TLV70233QDBVRQ1, probably",https://www.mouser.com/ProductDetail/863-NCP161ASN330T1G,
U5,1,,,Power Board,"Can also use other boards, see github for compatibility notes",https://github.com/MouseBiteLabs/Pocket-Mouse-Power-Board,
U6,1,TPS3840DL35,SOT23-5,Supervisory IC,,https://www.mouser.com/ProductDetail/Texas-Instruments/TPS38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,
U7,1,TL331,SOT23-5,Comparator,,https://www.mouser.com/ProductDetail/Texas-Instruments/TL331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,
VR1,1,10k (x2),,Volume wheel,Can be salvaged from MGB/CGB instead,https://retrogamerepairshop.com/collections/gbp-accessories/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,
X1,1,8.388608MHz,7.5X5-4-PAD,Crystal oscillator,,Salvaged (GBC),

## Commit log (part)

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2023-02-19 Add a lot of stuff
2023-02-19 Update BOM table
2023-02-19 Fix spacing
2023-02-20 Add assembly notes
2023-02-20 Update README.md
    Add assembly note
2023-02-20 Add BOM
2023-02-20 Typo
2023-02-20 Update power board BOM
2023-02-20 Update BOM
2023-02-24 Update Mouser cart
2023-02-24 chore(readme): include battery contacts
2023-03-12 Fix typo
2023-04-16 Rename MGBC-MBL-01/README.md to MGBC PCB/README.md
2023-04-17 Add audio recordings
2023-04-18 Move beta tester information to separate folder
2023-04-18 Add mouser cart links
2023-07-14 Update power draw measurements
2023-07-15 Added battery discharge curves
2023-08-01 Added information about alkaline batteries
2024-08-21 Update EM6-8 part number

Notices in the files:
MGBC PCB/README.md:
License:
This work is licensed under a Creative Commons Attribution-ShareAlike 4.0 International License. You are able to copy and redistribute the material in any medium or format, as well as remix, transform, or build upon the material for any purpose (even commercial) - but you **must** give appropriate credit, provide a link to
©MouseBiteLabs 2023
